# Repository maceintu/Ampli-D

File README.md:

# Ampli-D

Amplificateur audio stéréo **classe D** open hardware : entrées filaires et Bluetooth, DAC audiophile,
pilotage par microcontrôleur STM32. Le dépôt contient l'ensemble de la conception — schémas, PCB et firmware.

> **État du projet :** conception matérielle terminée côté schémas, routage du PCB en cours,
> firmware au stade du squelette généré (STM32CubeMX).

---

## Aperçu

## Caractéristiques

| Bloc | Composant principal | Rôle |
|------|--------------------|------|
| **Amplification** | TI **TPA3255** (DDV) | Étage de puissance classe D stéréo, filtres de sortie 10 µH / 25 A |
| **DAC** | TI **PCM5242** | Conversion I2S → analogique différentiel, sortie directe vers l'ampli |
| **Sélecteur de source** | TI **TMUX1574** | Aiguillage des flux I2S (filaire / Bluetooth) |
| **Entrées filaires** | TI **PCM1863** | 3 entrées stéréo numérisées (jacks Neutrik NMJ4HFD2 + jack 3,5 mm) |
| **Bluetooth** | **FSC-BT1058** | Réception audio sans fil (I2S) + contrôle par UART |
| **Contrôle** | ST **STM32G030C8T6** | Sélection de source, volume/EQ via I2C, appairage BT, gestion des défauts |
| **Alimentation** | LM5017 · TLV76733 · LT3042 | 36–48 V d'entrée → 12 V → 3,3 V numérique + 3,3 V analogique faible bruit |

**Interface utilisateur :** commutateur rotatif 4 positions (source), bouton poussoir (appairage Bluetooth),
4 potentiomètres lus par l'ADC du STM32 (volume et égalisation).

## Structure du dépôt

```
Ampli-D/
├── Kicad Workspace/        # Projet KiCad 10 (schémas hiérarchiques + PCB 2 couches)
│   ├── alimentation.kicad_sch
│   ├── amplification.kicad_sch
│   ├── bluetooth.kicad_sch
│   ├── eq_and_dac.kicad_sch
│   ├── mcu.kicad_sch
│   ├── wired_input.kicad_sch
│   ├── Components Lib.kicad_sym    # Symboles personnalisés
│   ├── FootPrints.pretty/          # Empreintes personnalisées
│   └── Lib Import/                 # Symboles / empreintes / STEP fabricants
├── STM32 Workspace/        # Projet STM32CubeIDE (STM32G030C8T6)
│   ├── MCU.ioc                     # Configuration CubeMX
│   ├── Core/                       # Code applicatif
│   └── Drivers/                    # HAL STM32G0 + CMSIS
└── Ressources/             # Datasheets, modèles 3D, outils de calcul
```

## Alimentation

| Rail | Régulateur | Usage |
|------|-----------|-------|
| 36 V / 48 V | entrée externe | PVDD du TPA3255 |
| 12 V | LM5017 (buck 100 V) | GVDD / pilotage de l'étage de puissance |
| 3,3 V | TLV76733 | Numérique (STM32, Bluetooth) |
| 3,3 V A | LT3042 (LDO ultra faible bruit) | Analogique (DAC, ADC) |

## Démarrage

**Matériel** — ouvrir le projet avec [KiCad](https://www.kicad.org/) **10.0 ou supérieur** :

```bash
kicad "Kicad Workspace/Kicad Workspace.kicad_pro"
```

**Firmware** — ouvrir `STM32 Workspace/` dans [STM32CubeIDE](https://www.st.com/en/development-tools/stm32cubeide.html),
puis compiler et flasher via ST-Link. La configuration des périphériques se modifie depuis `MCU.ioc`
(I2C1, USART1, ADC1 + DMA, TIM1).

## Feuille de route

- [x] Schémas des six blocs fonctionnels
- [x] Symboles et empreintes des composants clés (TPA3255, PCM5242, FSC-BT1058, inductances de sortie)
- [ ] Routage complet du PCB
- [ ] Firmware : sélection de source, contrôle I2C du DAC/ADC, lecture des potentiomètres, gestion des défauts
- [ ] Fabrication et validation du premier prototype

## Ressources

Les datasheets de tous les circuits intégrés sont regroupées dans
[`Ressources/Datasheet/`](Ressources/Datasheet/), nommées par leur référence dans le schéma
(`U1_FSC-BT1058.pdf`, `U5_TPA3255.pdf`…). Le sous-dossier `txt/` en contient le texte intégral,
balisé page par page, pour pouvoir chercher dans l'ensemble de la documentation d'un seul coup :

```bash
grep -rn "bootstrap" Ressources/Datasheet/txt/
```

L'index [`Ressources/Datasheet/README.md`](Ressources/Datasheet/README.md) donne pour chaque
composant son rôle, la révision du document et la page où trouver brochage, maxima absolus,
caractéristiques électriques, layout et table des registres.

Le classeur `LM5017QuickStartCalculator.xls` sert au dimensionnement du convertisseur.

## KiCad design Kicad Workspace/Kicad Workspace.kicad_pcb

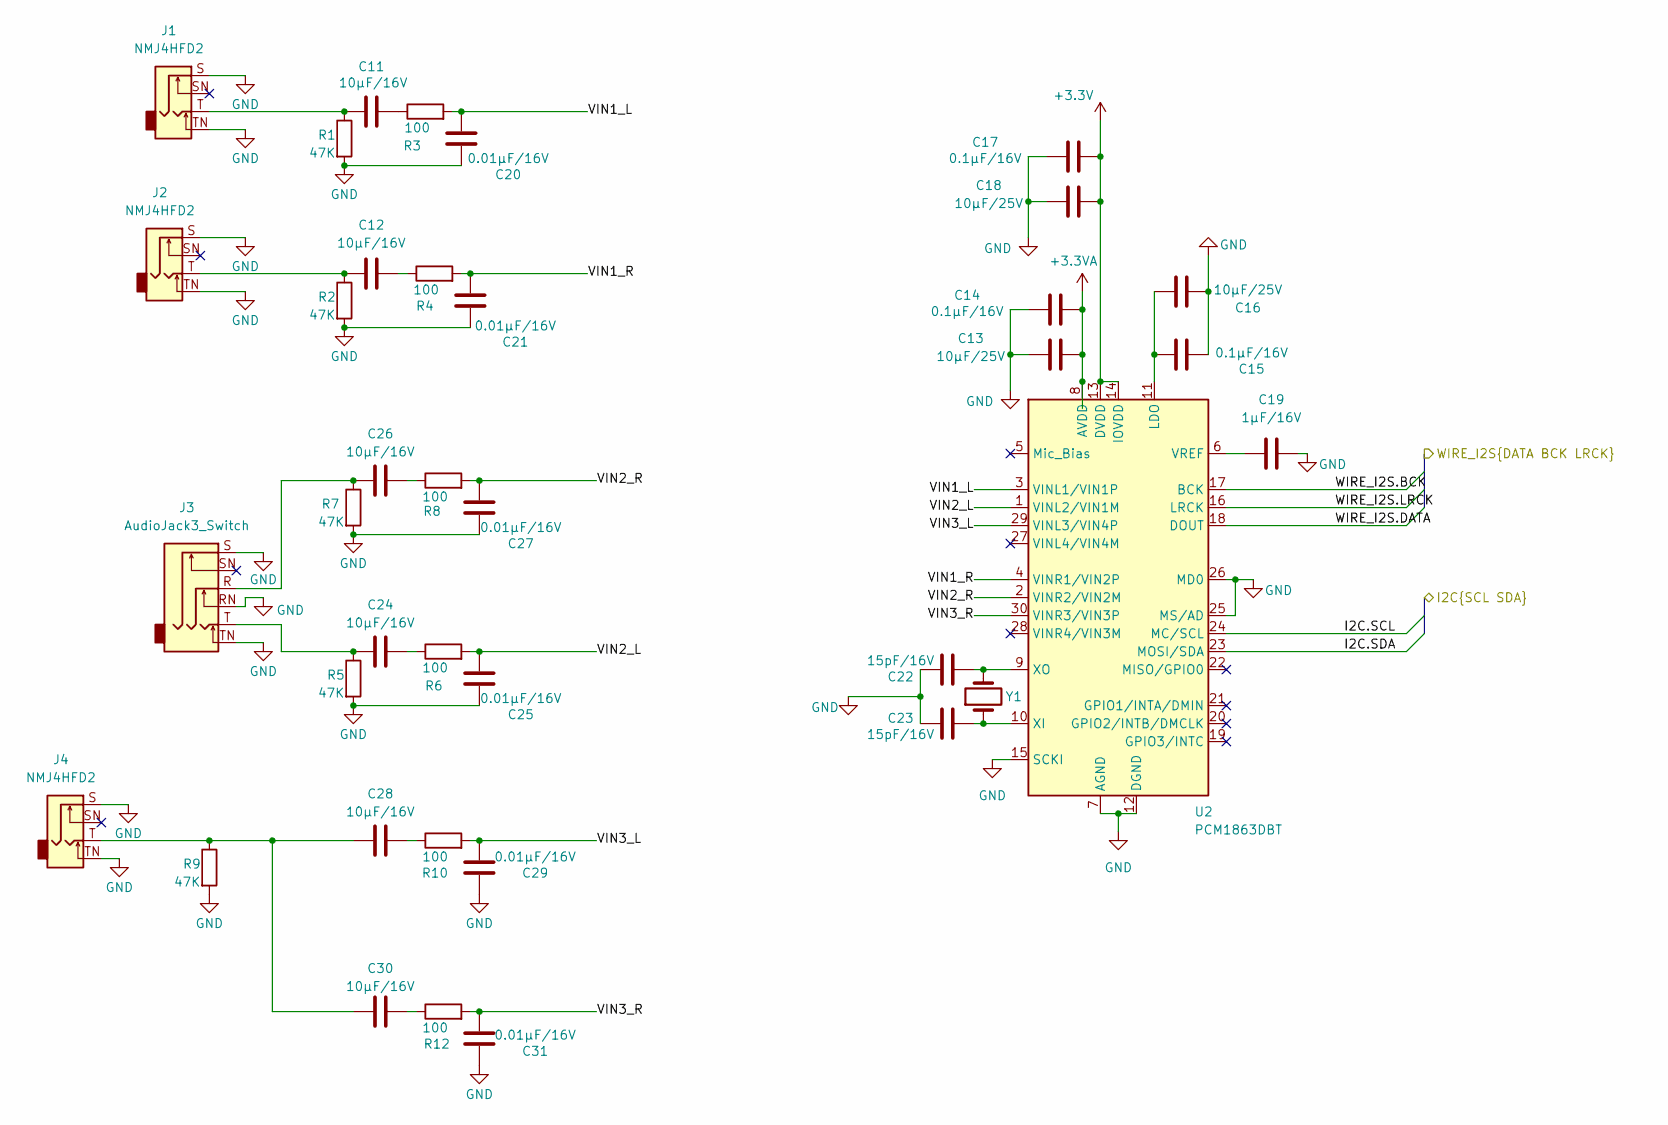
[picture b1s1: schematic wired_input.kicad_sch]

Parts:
C11, C12, C24, C26, C28, C30: 10µF/16V; C_0805_2012Metric
C13, C16, C18: 10µF/25V; C_0805_2012Metric
C14, C15, C17: 0.1µF/16V; C_0402_1005Metric
C19: 1µF/16V; C_0805_2012Metric
C20, C21, C25, C27, C29, C31: 0.01µF/16V; C_0402_1005Metric
C22, C23: 15pF/16V; C_0402_1005Metric
J1, J2, J4: NMJ4HFD2; Jack_6.35mm_Neutrik_NMJ4HFD2_Horizontal
J3: AudioJack3_Switch; Jack_3.5mm_CUI_SJ1-3535NG_Horizontal
R1, R2, R5, R7, R9: 47K; R_01005_0402Metric
R3, R4, R6, R8, R10, R12: 100; R_01005_0402Metric
U2: PCM1863DBT; TSSOP-30_4.4x7.8mm_P0.5mm
Y1: Crystal

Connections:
+3.3V: C17.1, C18.1, U2.13 (DVDD), U2.14 (IOVDD); also elsewhere on the board
+3.3VA: C13.1, C14.1, U2.8 (AVDD); also elsewhere on the board
/EQ and DAC/I2C.SCL: U2.24 (MC/SCL); also elsewhere on the board
/EQ and DAC/I2C.SDA: U2.23 (MOSI/SDA); also elsewhere on the board
/EQ and DAC/WIRE_I2S.BCK: U2.17 (BCK); also elsewhere on the board
/EQ and DAC/WIRE_I2S.DATA: U2.18 (DOUT); also elsewhere on the board
/EQ and DAC/WIRE_I2S.LRCK: U2.16 (LRCK); also elsewhere on the board
/Wired Input/VIN1_L: C20.1, R3.2, U2.3 (VINL1/VIN1P)
/Wired Input/VIN1_R: C21.1, R4.2, U2.4 (VINR1/VIN2P)
/Wired Input/VIN2_L: C25.1, R6.2, U2.1 (VINL2/VIN1M)
/Wired Input/VIN2_R: C27.1, R8.2, U2.2 (VINR2/VIN2M)
/Wired Input/VIN3_L: C29.1, R10.2, U2.29 (VINL3/VIN4P)
/Wired Input/VIN3_R: C31.1, R12.2, U2.30 (VINR3/VIN3P)
GND: C13.2, C14.2, C15.2, C16.2, C17.2, C18.2, C19.2, C20.2, C21.2, C22.2, C23.1, C25.2, C27.2, C29.2, C31.2, J1.S, J1.TN, J2.S, J2.TN, J3.RN, J3.S, J3.TN, J4.S, J4.TN, R1.2, R2.2, R5.2, R7.2, R9.2, U2.7 (AGND), U2.12 (DGND), U2.15 (SCKI), U2.25 (MS/AD), U2.26 (MD0); also elsewhere on the board
unnamed: C11.1, J1.T, R1.1
unnamed: C11.2, R3.1
unnamed: C12.1, J2.T, R2.1
unnamed: C12.2, R4.1
unnamed: C24.1, J3.T, R5.1
unnamed: C24.2, R6.1
unnamed: C26.1, J3.R, R7.1
unnamed: C26.2, R8.1
unnamed: C28.1, C30.1, J4.T, R9.1
unnamed: C28.2, R10.1
unnamed: C30.2, R12.1
unnamed: C15.1, C16.1, U2.11 (LDO)
unnamed: C19.1, U2.6 (VREF)
unnamed: C23.2, U2.10 (XI), Y1.1
unnamed: C22.1, U2.9 (XO), Y1.2

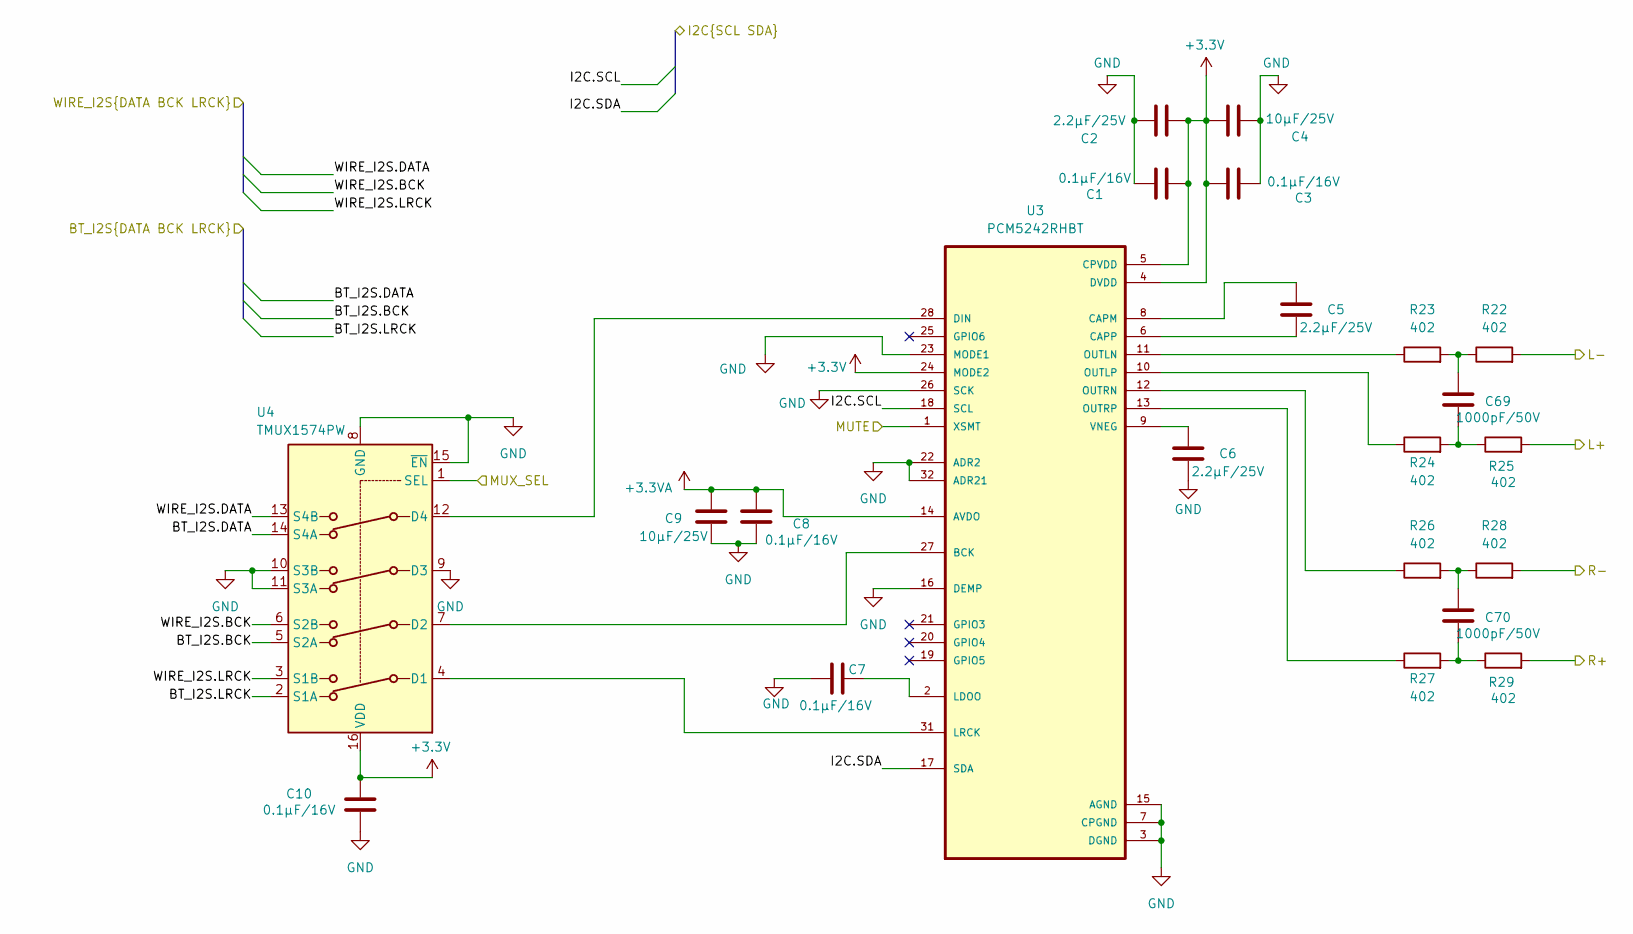
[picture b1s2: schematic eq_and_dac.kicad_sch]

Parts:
C1, C3, C7, C8, C10: 0.1µF/16V; C_0402_1005Metric
C2, C6: 2.2µF/25V; C_0805_2012Metric
C4, C9: 10µF/25V; C_0805_2012Metric
C5: 2.2µF/25V; C_0201_0603Metric
C69, C70: 1000pF/50V; C_0201_0603Metric
R22, R23, R24, R25, R26, R27, R28, R29: 402; R_0201_0603Metric
U3: PCM5242RHBT; PCM5242
U4: TMUX1574PW; TSSOP-16_4.4x5mm_P0.65mm

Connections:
+3.3V: C1.2, C2.2, C3.1, C4.1, C10.2, U3.4 (DVDD), U3.5 (CPVDD), U3.24 (MODE2), U4.16 (VDD); also elsewhere on the board
+3.3VA: C8.2, C9.2, U3.14 (AVDO); also elsewhere on the board
/Amplification/IN_L+: R25.2; also elsewhere on the board
/Amplification/IN_L-: R22.2; also elsewhere on the board
/Amplification/IN_R+: R29.2; also elsewhere on the board
/Amplification/IN_R-: R28.2; also elsewhere on the board
/Bluetooth/BT_I2S.BCK: U4.5 (S2A); also elsewhere on the board
/Bluetooth/BT_I2S.DATA: U4.14 (S4A); also elsewhere on the board
/Bluetooth/BT_I2S.LRCK: U4.2 (S1A); also elsewhere on the board
/EQ and DAC/I2C.SCL: U3.18 (SCL); also elsewhere on the board
/EQ and DAC/I2C.SDA: U3.17 (SDA); also elsewhere on the board
/EQ and DAC/MUTE: U3.1 (XSMT); also elsewhere on the board
/EQ and DAC/MUX_SEL: U4.1 (SEL); also elsewhere on the board
/EQ and DAC/WIRE_I2S.BCK: U4.6 (S2B); also elsewhere on the board
/EQ and DAC/WIRE_I2S.DATA: U4.13 (S4B); also elsewhere on the board
/EQ and DAC/WIRE_I2S.LRCK: U4.3 (S1B); also elsewhere on the board
GND: C1.1, C2.1, C3.2, C4.2, C6.2, C7.1, C8.1, C9.1, C10.1, U3.3 (DGND), U3.7 (CPGND), U3.15 (AGND), U3.16 (DEMP), U3.22 (ADR2), U3.23 (MODE1), U3.26 (SCK), U3.32 (ADR21), U4.8 (GND), U4.9 (D3), U4.10 (S3B), U4.11 (S3A), U4.15 (~EN); also elsewhere on the board
unnamed: C69.1, R24.2, R25.1
unnamed: C69.2, R22.1, R23.2
unnamed: C70.1, R27.2, R29.1
unnamed: C70.2, R26.2, R28.1
unnamed: U3.27 (BCK), U4.7 (D2)
unnamed: C5.1, U3.8 (CAPM)
unnamed: C5.2, U3.6 (CAPP)
unnamed: U3.28 (DIN), U4.12 (D4)
unnamed: C7.2, U3.2 (LDOO)
unnamed: U3.31 (LRCK), U4.4 (D1)
unnamed: R23.1, U3.11 (OUTLN)
unnamed: R24.1, U3.10 (OUTLP)
unnamed: R26.1, U3.12 (OUTRN)
unnamed: R27.1, U3.13 (OUTRP)
unnamed: C6.1, U3.9 (VNEG)

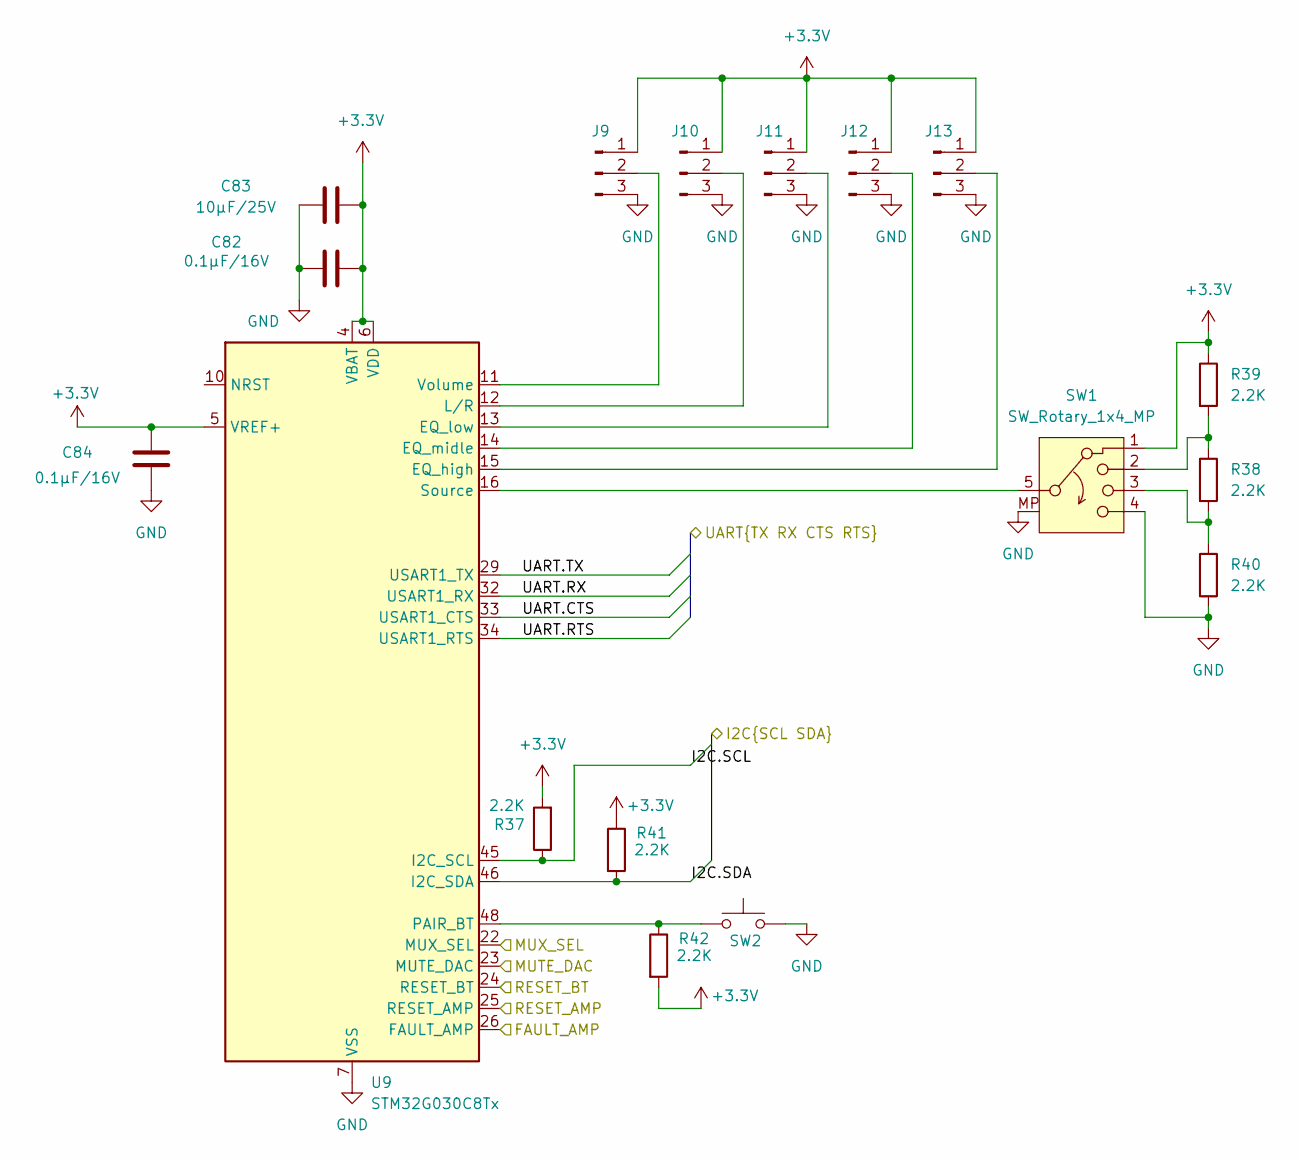
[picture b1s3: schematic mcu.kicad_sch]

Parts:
C82, C84: 0.1µF/16V; C_0402_1005Metric
C83: 10µF/25V; C_0805_2012Metric
J9, J10, J11, J12, J13: Conn_01x03_Pin; PinHeader_1x03_P2.54mm_Vertical
R37, R38, R39, R40, R41, R42: 2.2K; R_0201_0603Metric
SW1: SW_Rotary_1x4_MP
SW2: SW_PUSH_6mm
U9: STM32G030C8Tx; LQFP-48_7x7mm_P0.5mm

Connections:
+3.3V: C82.1, C83.1, C84.2, J9.1, J10.1, J11.1, J12.1, J13.1, R37.2, R39.1, R41.1, R42.2, SW1.1, U9.4 (VBAT), U9.5 (VREF+), U9.6 (VDD); also elsewhere on the board
/Amplification/FAULT: U9.26 (FAULT_AMP); also elsewhere on the board
/Amplification/RESET: U9.25 (RESET_AMP); also elsewhere on the board
/Bluetooth/BT_RESET: U9.24 (RESET_BT); also elsewhere on the board
/Bluetooth/UART.CTS: U9.33 (USART1_CTS); also elsewhere on the board
/Bluetooth/UART.RTS: U9.34 (USART1_RTS); also elsewhere on the board
/Bluetooth/UART.RX: U9.32 (USART1_RX); also elsewhere on the board
/Bluetooth/UART.TX: U9.29 (USART1_TX); also elsewhere on the board
/EQ and DAC/I2C.SCL: R37.1, U9.45 (I2C_SCL); also elsewhere on the board
/EQ and DAC/I2C.SDA: R41.2, U9.46 (I2C_SDA); also elsewhere on the board
/EQ and DAC/MUTE: U9.23 (MUTE_DAC); also elsewhere on the board
/EQ and DAC/MUX_SEL: U9.22 (MUX_SEL); also elsewhere on the board
GND: C82.2, C83.2, C84.1, J9.3, J10.3, J11.3, J12.3, J13.3, R40.2, SW1.4, SW1.MP, SW2.2, U9.7 (VSS); also elsewhere on the board
unnamed: J9.2, U9.11 (Volume)
unnamed: J10.2, U9.12 (L/R)
unnamed: J11.2, U9.13 (EQ_low)
unnamed: J12.2, U9.14 (EQ_midle)
unnamed: J13.2, U9.15 (EQ_high)
unnamed: R38.1, R39.2, SW1.2
unnamed: R38.2, R40.1, SW1.3
unnamed: R42.1, SW2.1, U9.48 (PAIR_BT)
unnamed: SW1.5, U9.16 (Source)

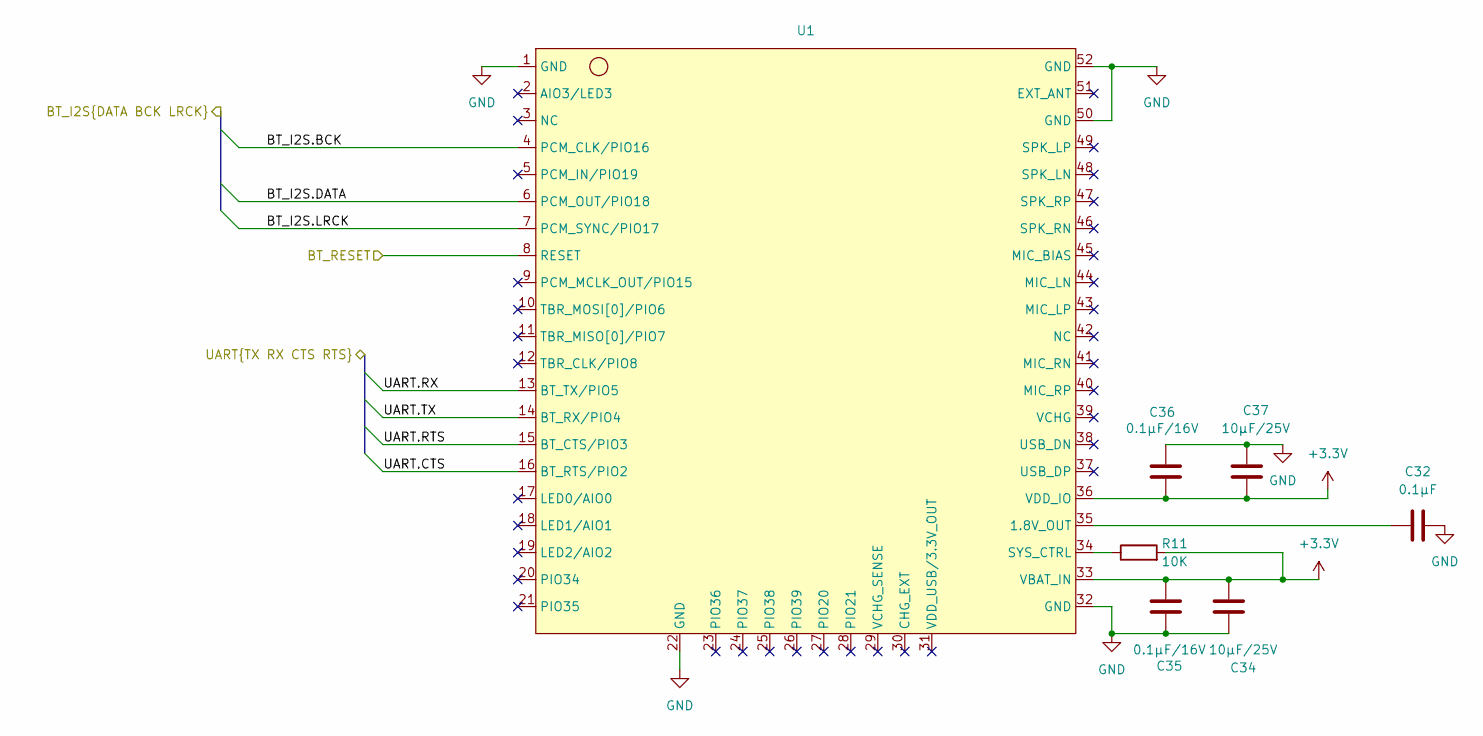
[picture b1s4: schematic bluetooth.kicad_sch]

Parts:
C32: 0.1µF; C_01005_0402Metric
C34, C37: 10µF/25V; C_0805_2012Metric
C35, C36: 0.1µF/16V; C_0402_1005Metric
R11: 10K; R_0402_1005Metric
U1: FSC-BT1058

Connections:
+3.3V: C34.1, C35.1, C36.1, C37.1, R11.2, U1.33 (VBAT_IN), U1.36 (VDD_IO); also elsewhere on the board
/Bluetooth/BT_I2S.BCK: U1.4 (PCM_CLK/PIO16); also elsewhere on the board
/Bluetooth/BT_I2S.DATA: U1.6 (PCM_OUT/PIO18); also elsewhere on the board
/Bluetooth/BT_I2S.LRCK: U1.7 (PCM_SYNC/PIO17); also elsewhere on the board
/Bluetooth/BT_RESET: U1.8 (RESET); also elsewhere on the board
/Bluetooth/UART.CTS: U1.16 (BT_RTS/PIO2); also elsewhere on the board
/Bluetooth/UART.RTS: U1.15 (BT_CTS/PIO3); also elsewhere on the board
/Bluetooth/UART.RX: U1.13 (BT_TX/PIO5); also elsewhere on the board
/Bluetooth/UART.TX: U1.14 (BT_RX/PIO4); also elsewhere on the board
GND: C32.2, C34.2, C35.2, C36.2, C37.2, U1.1 (GND), U1.22 (GND), U1.32 (GND), U1.50 (GND), U1.52 (GND); also elsewhere on the board
unnamed: C32.1, U1.35 (1.8V_OUT)
unnamed: R11.1, U1.34 (SYS_CTRL)

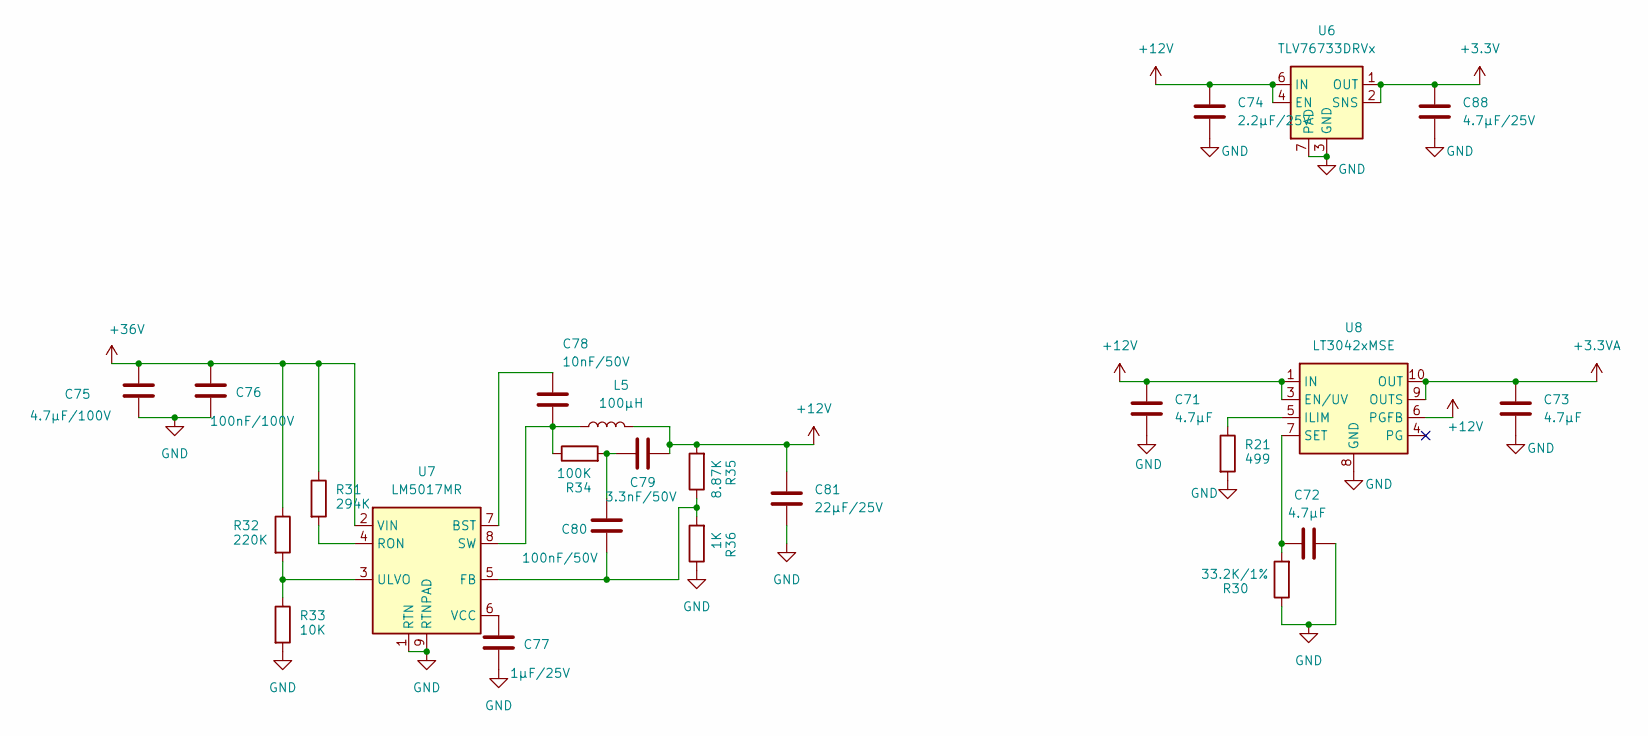
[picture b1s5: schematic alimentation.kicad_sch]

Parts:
C71, C72, C73: 4.7µF; C_0805_2012Metric
C74: 2.2µF/25V; C_0603_1608Metric
C75: 4.7µF/100V; C_1210_3225Metric
C76: 100nF/100V; C_0805_2012Metric
C77: 1µF/25V; C_0805_2012Metric
C78: 10nF/50V; C_0603_1608Metric
C79: 3.3nF/50V; C_0603_1608Metric
C80: 100nF/50V; C_0603_1608Metric
C81: 22µF/25V; C_1210_3225Metric
C88: 4.7µF/25V; C_0603_1608Metric
L5: 100µH; L_Bourns_SRR1260
R21: 499; R_0201_0603Metric
R30: 33.2K/1%; R_0805_2012Metric
R31: 294K; R_0603_1608Metric
R32: 220K; R_0603_1608Metric
R33: 10K; R_0603_1608Metric
R34: 100K; R_0603_1608Metric
R35: 8.87K; R_0603_1608Metric
R36: 1K; R_0603_1608Metric
U6: TLV76733DRVx; WSON-6-1EP_2x2mm_P0.65mm_EP1x1.6mm_ThermalVias
U7: LM5017MR; SOIC-8-1EP_3.9x4.9mm_P1.27mm_EP2.95x4.9mm_Mask2.71x3.4mm_Th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
U8: LT3042xMSE; MSOP-10-1EP_3x3mm_P0.5mm_EP1.68x1.88mm

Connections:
+3.3V: C88.1, U6.1 (OUT), U6.2 (SNS); also elsewhere on the board
+3.3VA: C73.1, U8.9 (OUTS), U8.10 (OUT); also elsewhere on the board
+12V: C71.1, C74.1, C79.2, C81.1, L5.2, R35.2, U6.4 (EN), U6.6 (IN), U8.1 (IN), U8.2 (IN), U8.3 (EN/UV), U8.6 (PGFB); also elsewhere on the board
+36V: C75.2, C76.2, R31.1, R32.1, U7.2 (VIN); also elsewhere on the board
GND: C71.2, C72.2, C73.2, C74.2, C75.1, C76.1, C77.1, C81.2, C88.2, R21.2, R30.1, R33.2, R36.1, U6.3 (GND), U6.5 (GND), U6.7 (PAD), U7.1 (RTN), U7.9 (RTNPAD), U8.8 (GND), U8.11 (GND); also elsewhere on the board
unnamed: C79.1, C80.2, R34.2
unnamed: C78.1, U7.7 (BST)
unnamed: C80.1, R35.1, R36.2, U7.5 (FB)
unnamed: R31.2, U7.4 (RON)
unnamed: C78.2, L5.1, R34.1, U7.8 (SW)
unnamed: R32.2, R33.1, U7.3 (ULVO)
unnamed: C77.2, U7.6 (VCC)
unnamed: R21.1, U8.5 (ILIM)
unnamed: C72.1, R30.2, U8.7 (SET)

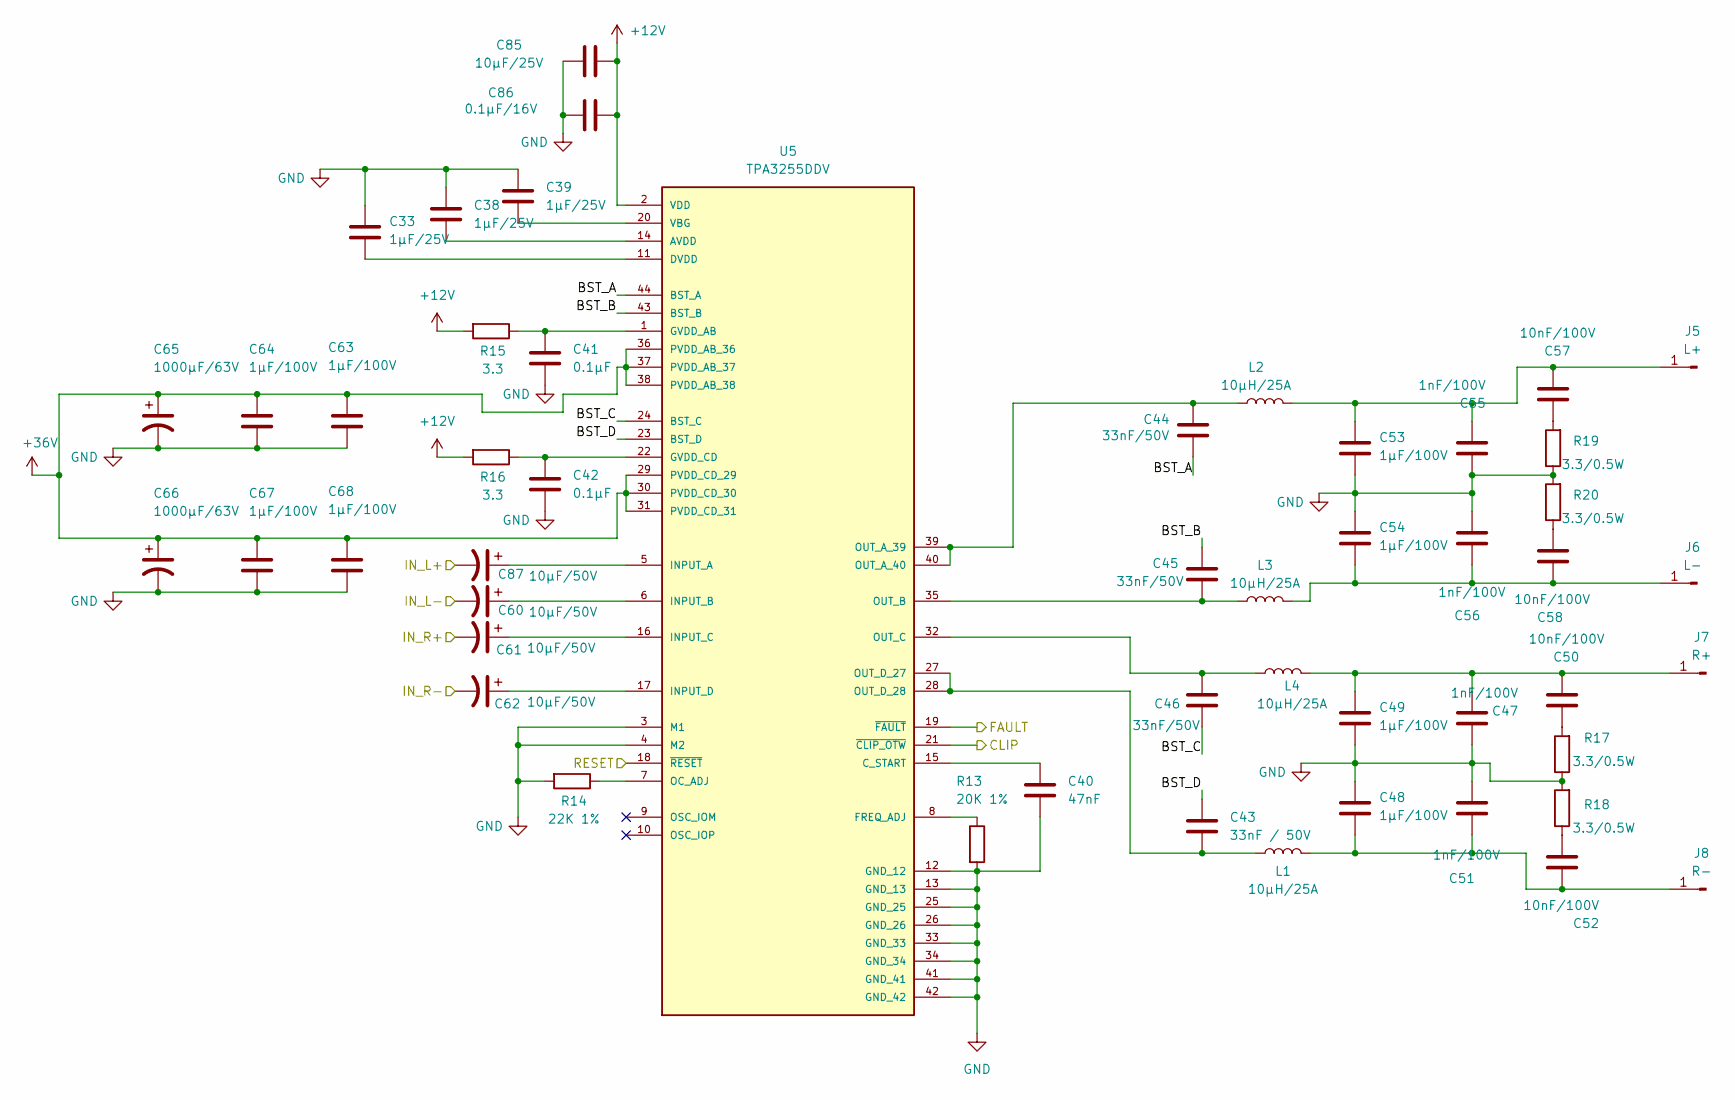
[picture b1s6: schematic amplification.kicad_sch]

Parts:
C33, C38, C39: 1µF/25V; C_0603_1608Metric
C40: 47nF; C_0201_0603Metric
C41, C42: 0.1µF; C_0603_1608Metric
C43: 33nF / 50V; C_0603_1608Metric
C44, C45, C46: 33nF/50V; C_0603_1608Metric
C47, C51, C55, C56: 1nF/100V; C_0201_0603Metric
C48, C49, C53, C54: 1µF/100V; C_Rect_L10.0mm_W4.0mm_P7.50mm_MKS4
C50, C52, C57, C58: 10nF/100V; C_0805_2012Metric
C60, C61, C62, C87: 10µF/50V; CP_Radial_D6.3mm_P2.50mm
C63, C64, C67, C68: 1µF/100V; C_1206_3216Metric
C65, C66: 1000µF/63V; CP_Radial_D16.0mm_P7.50mm
C85: 10µF/25V; C_0805_2012Metric
C86: 0.1µF/16V; C_0402_1005Metric
J5: L+; SolderWirePad_1x01_SMD_2x4mm
J6: L-; SolderWirePad_1x01_SMD_2x4mm
J7: R+; SolderWirePad_1x01_SMD_2x4mm
J8: R-; SolderWirePad_1x01_SMD_2x4mm
L1, L2, L3, L4: 10µH/25A; IND_SER2915L-103KL
R13: 20K 1%; R_0805_2012Metric
R14: 22K 1%; R_0805_2012Metric
R15, R16: 3.3; R_0201_0603Metric
R17, R18, R19, R20: 3.3/0.5W; R_1206_3216Metric
U5: TPA3255DDV; TPA3255; PARTREV A

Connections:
+12V: C85.1, C86.1, R15.2, R16.2, U5.2 (VDD); also elsewhere on the board
+36V: C63.1, C64.1, C65.1, C66.1, C67.1, C68.1, U5.29 (PVDD_CD_29), U5.30 (PVDD_CD_30), U5.31 (PVDD_CD_31), U5.36 (PVDD_AB_36), U5.37 (PVDD_AB_37), U5.38 (PVDD_AB_38); also elsewhere on the board
/Amplification/BST_A: C44.2, U5.44 (BST_A)
/Amplification/BST_B: C45.1, U5.43 (BST_B)
/Amplification/BST_C: C46.2, U5.24 (BST_C)
/Amplification/BST_D: C43.1, U5.23 (BST_D)
/Amplification/CLIP: U5.21 (~CLIP_OTW)
/Amplification/FAULT: U5.19 (~FAULT); also elsewhere on the board
/Amplification/IN_L+: C87.2; also elsewhere on the board
/Amplification/IN_L-: C60.2; also elsewhere on the board
/Amplification/IN_R+: C61.2; also elsewhere on the board
/Amplification/IN_R-: C62.2; also elsewhere on the board
/Amplification/RESET: U5.18 (~RESET); also elsewhere on the board
GND: C33.1, C38.2, C39.2, C40.2, C41.1, C42.1, C47.1, C48.1, C49.2, C51.2, C53.2, C54.1, C55.1, C56.2, C63.2, C64.2, C65.2, C66.2, C67.2, C68.2, C85.2, C86.2, R13.2, R14.2, R17.1, R18.2, R19.1, R20.2, U5.3 (M1), U5.4 (M2), U5.12 (GND_12), U5.13 (GND_13), U5.25 (GND_25), U5.26 (GND_26), U5.33 (GND_33), U5.34 (GND_34), U5.41 (GND_41), U5.42 (GND_42); also elsewhere on the board
unnamed: C50.1, R17.2
unnamed: C52.2, R18.1
unnamed: C57.1, R19.2
unnamed: C58.2, R20.1
unnamed: C53.1, C55.2, C57.2, J5.1 (Pin_1_1), L2.2
unnamed: C54.2, C56.1, C58.1, J6.1 (Pin_1_1), L3.2
unnamed: C47.2, C49.1, C50.2, J7.1 (Pin_1_1), L4.2
unnamed: C48.2, C51.1, C52.1, J8.1 (Pin_1_1), L1.2
unnamed: C38.1, U5.14 (AVDD)
unnamed: C40.1, U5.15 (C_START)
unnamed: C33.2, U5.11 (DVDD)
unnamed: R13.1, U5.8 (FREQ_ADJ)
unnamed: C41.2, R15.1, U5.1 (GVDD_AB)
unnamed: C42.2, R16.1, U5.22 (GVDD_CD)
unnamed 91: C87.1, U5.5 (INPUT_A); also elsewhere on the board
unnamed 92: C60.1, U5.6 (INPUT_B); also elsewhere on the board
unnamed 93: C61.1, U5.16 (INPUT_C); also elsewhere on the board
unnamed 94: C62.1, U5.17 (INPUT_D); also elsewhere on the board
unnamed: R14.1, U5.7 (OC_ADJ)
unnamed: C44.1, L2.1, U5.39 (OUT_A_39), U5.40 (OUT_A_40)
unnamed: C45.2, L3.1, U5.35 (OUT_B)
unnamed: C46.1, L4.1, U5.32 (OUT_C)
unnamed: C43.2, L1.1, U5.27 (OUT_D_27), U5.28 (OUT_D_28)
unnamed: C39.1, U5.20 (VBG)

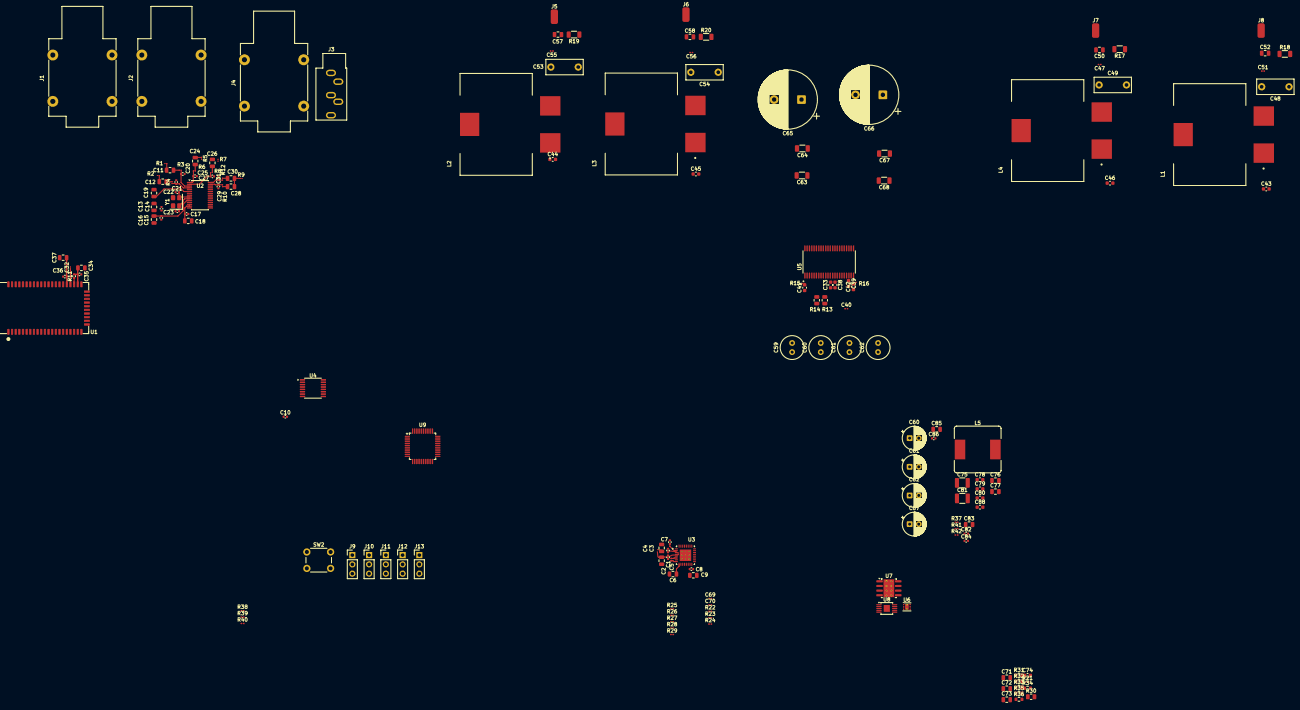
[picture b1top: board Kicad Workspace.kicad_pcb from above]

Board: 2 copper layers, 162 parts (0 on the bottom side), 109 nets.

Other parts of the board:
C59: 10µF/50V; C_Radial_D6.3mm_H11.0mm_P2.50mm
C60#2, C61#2, C62#2: 10µF/50V; CP_Radial_D6.3mm_P2.50mm

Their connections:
/Amplification/IN_L+: C59.2; also elsewhere on the board
/Amplification/IN_L-: C60#2.2; also elsewhere on the board
/Amplification/IN_R+: C61#2.2; also elsewhere on the board
/Amplification/IN_R-: C62#2.2; also elsewhere on the board
unnamed 91: C59.1; also elsewhere on the board
unnamed 92: C60#2.1; also elsewhere on the board
unnamed 93: C61#2.1; also elsewhere on the board
unnamed 94: C62#2.1; also elsewhere on the board

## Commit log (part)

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2026-05-26 deleting sublime merge parasite files
2026-05-26 Adding global scematic
2026-05-27 more doc
2026-05-28 more doc (MUX + ADC)
2026-05-31 kicad project
2026-06-01 feat: MUX + DAC Kicad schematics done
2026-06-02 Wire input (ADC) schematics done
2026-06-03 feat: Bluetooth FSC BT1058 schematics done
2026-06-03 feat: ampli stage work in progress
2026-06-03 kicad_prl
2026-06-03 pro and sch update
2026-06-03 add gitignore
2026-06-03 project update
2026-06-04 feat: filtering analog output
2026-06-04 feat: TPA3255 power 48V + clean output
2026-06-04 feat: project global
2026-06-06 feat: alimentation stage almost done
2026-06-06 fix: split analog 3.3 from digital 3.3
2026-06-06 feat: calculator for the LM5017 capa/resistor values
2026-06-07 feat: alim stage done + adapt to 36V input voltage instead of 48
2026-06-08 feat: mcu stm32 stack project
2026-06-08 feat: kicad mcu routing work in progress
2026-06-08 feat: mcu routing work in progress
2026-06-09 feat: pin declaration cube MX + 2DC + 1 ADC channel
2026-06-09 feat: code update with new pins
2026-06-09 feat: kicad mcu symbole modif to match pins
2026-06-10 feat: schematics almost done, starting to correct compile pb
2026-06-10 feat: correction work in progress
2026-06-11 feat: start of routing
2026-06-14 feat: BT1058 footprint
2026-06-14 feat: BT-1058 footprint name update
2026-06-14 feat: adding jack connectors on PCB
2026-06-15 ressources: jack 3d files
2026-06-15 feat: jack schematics
2026-06-15 fix: Bus fix with correct syntax
2026-06-15 ressource: PCM5242 & TPA3255 footprint
2026-06-15 feat: routing work in progress
2026-06-16 feat: potentiometers + source switch + bt pari button
2026-06-17 feat: selecting TPA3255 output inductances
2026-06-17 feat: routing TPA3255 output components placement
